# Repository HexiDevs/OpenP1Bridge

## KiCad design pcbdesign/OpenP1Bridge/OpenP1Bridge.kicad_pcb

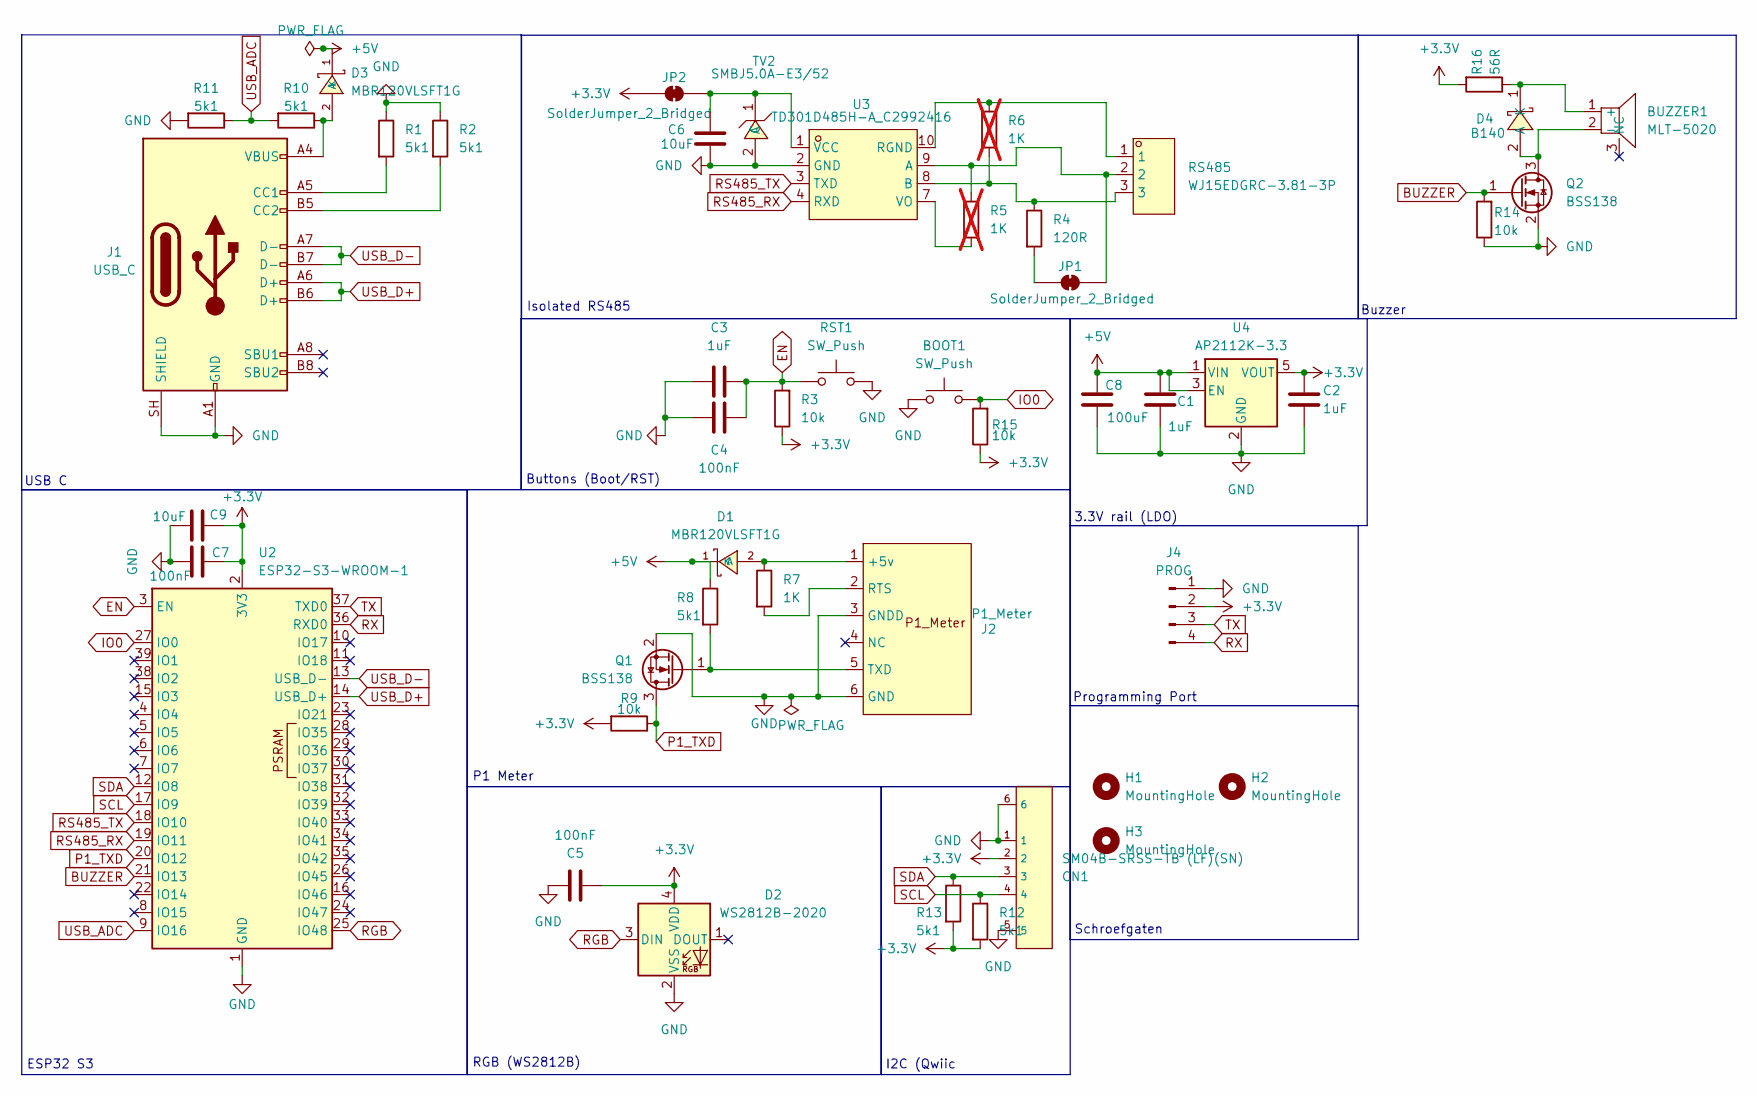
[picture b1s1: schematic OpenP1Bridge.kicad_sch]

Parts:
BOOT1: SW_Push; SW_SPST_B3U-1000P
BUZZER1: MLT-5020; BUZ-SMD_L5.0-W5.5-P4.60; MPN MLT-5020; LCSC Part C94598
C1, C2: 1uF; C_0805_2012Metric
C3: 1uF; C_0603_1608Metric
C4, C5, C7: 100nF; C_0603_1608Metric
C6, C9: 10uF; C_0805_2012Metric
C8: 100uF; C_1206_3216Metric
CN1: SM04B-SRSS-TB (LF)(SN); C160404_CONN-SMD_4P-P1_00_SM04B-SRSS-TB-LF-SN; LCSC C160404
D1, D3: MBR120VLSFT1G; C223608_SOD-123F_L2_8-W1_8-LS3_7-RD; LCSC C223608
D2: WS2812B-2020; LED_WS2812B-2020_PLCC4_2.0x2.0mm
D4: B140; SMA_L4.3-W2.6-LS5.1-RD; MPN B140; LCSC Part C42414246
H1, H2, H3: MountingHole; MountingHole_3.2mm_M3_DIN965_Pad
J1: USB_C; USB_C_Receptacle_GCT_USB4105-xx-A_16P_TopMnt_Horizontal
J2: P1_Meter; P1_SolderPads
J4: PROG; Prog_pad
JP1, JP2: SolderJumper_2_Bridged; SolderJumper-2_P1.3mm_Bridged_RoundedPad1.0x1.5mm
Q1, Q2: BSS138; SOT-23
R1, R2, R8, R10, R11, R12, R13: 5k1; R_0603_1608Metric
R3, R9, R14, R15: 10k; R_0603_1608Metric
R4: 120R; R_1206_3216Metric
R5, R6: 1K; R_0805_2012Metric; not fitted
R7: 1K; R_0805_2012Metric
R16: 56R; R_0603_1608Metric
RS485: WJ15EDGRC-3.81-3P; CONN-TH_3P-P3.81_WJ15EDGRC-3.81-3P; MPN WJ15EDGRC-3.81-03P-14-00A; LCSC Part C8406
RST1: SW_Push; SW_SPST_B3U-1000P
TV2: SMBJ5.0A-E3/52; SMB_L4.6-W3.6-LS5.3-RD; MPN SMBJ5.0A-E3/52; LCSC Part C61069
U2: ESP32-S3-WROOM-1
U3: TD301D485H-A_C2992416; COMM-TH_TD301D485H-A-2; MPN TD301D485H-A; LCSC Part C2992416
U4: AP2112K-3.3; SOT-23-5

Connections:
+3.3V: C2.1, C5.2, C7.2, C9.2, CN1.2, D2.4 (VDD), J4.2, JP2.2 (B), R3.1, R9.2, R12.2, R13.2, R15.1, R16.2, U2.2 (3V3), U4.5 (VOUT); also elsewhere on the board
+5V: C1.1, C8.1, D1.1 (K), D3.1 (K), R8.1, U4.1 (VIN), U4.3 (EN)
BUZZER: Q2.1 (G), R14.2, U2.21 (IO13)
EN: C3.2, C4.1, R3.2, RST1.1, U2.3 (EN)
GND: BOOT1.1, C1.2, C2.2, C3.1, C4.2, C5.1, C6.2, C7.1, C8.2, C9.1, CN1.1, CN1.5, CN1.6, D2.2 (VSS), J1.A1 (GND), J1.A12 (GND), J1.B1 (GND), J1.B12 (GND), J1.SH (SHIELD), J2.3 (GNDD), J2.6 (GND), J4.1, Q1.2 (S), Q2.2 (S), R1.1, R2.1, R11.2, R14.1, RST1.2, TV2.2 (A), U2.1 (GND), U2.40 (GND), U2.41 (GND), U3.2 (GND), U4.2 (GND); also elsewhere on the board
IO0: BOOT1.2, R15.2, U2.27 (IO0)
unnamed: BUZZER1.1 (+), D4.1 (K), R16.1
unnamed: BUZZER1.2 (-), D4.2 (A), Q2.3 (D)
unnamed: D1.2 (A), J2.1 (+5v), R7.1
unnamed: D3.2 (A), J1.A4 (VBUS), J1.A9 (VBUS), J1.B4 (VBUS), J1.B9 (VBUS), R10.1
unnamed: J1.A5 (CC1), R1.2
unnamed: J1.B5 (CC2), R2.2
unnamed: J2.2 (RTS), R7.2
unnamed: J2.5 (TXD), Q1.1 (G), R8.2
unnamed: JP1.1 (A), R5.1, RS485.2, U3.9 (A)
unnamed: JP1.2 (B), R4.2
unnamed: C6.1, JP2.1 (A), TV2.1 (C), U3.1 (VCC)
unnamed: R4.1, R6.2, RS485.3, U3.8 (B)
unnamed: R6.1, RS485.1, U3.10 (RGND)
unnamed: R5.2, U3.7 (VO)
P1_TXD: Q1.3 (D), R9.1, U2.20 (IO12)
RGB: D2.3 (DIN), U2.25 (IO48)
RS485_RX: U2.19 (IO11), U3.4 (RXD)
RS485_TX: U2.18 (IO10), U3.3 (TXD)
RX: J4.4, U2.36 (RXD0); also elsewhere on the board
SCL: CN1.4, R12.1, U2.17 (IO9)
SDA: CN1.3, R13.1, U2.12 (IO8)
TX: J4.3, U2.37 (TXD0); also elsewhere on the board
USB_ADC: R10.2, R11.1, U2.9 (IO16)
USB_D+: J1.A6 (D+), J1.B6 (D+), U2.14 (USB_D+)
USB_D-: J1.A7 (D-), J1.B7 (D-), U2.13 (USB_D-)

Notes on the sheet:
ESP32 S3
RGB (WS2812B)
I2C (Qwiic
Buzzer
Isolated RS485
P1 Meter
USB C
3.3V rail (LDO)
Buttons (Boot/RST)
Programming Port
Schroefgaten

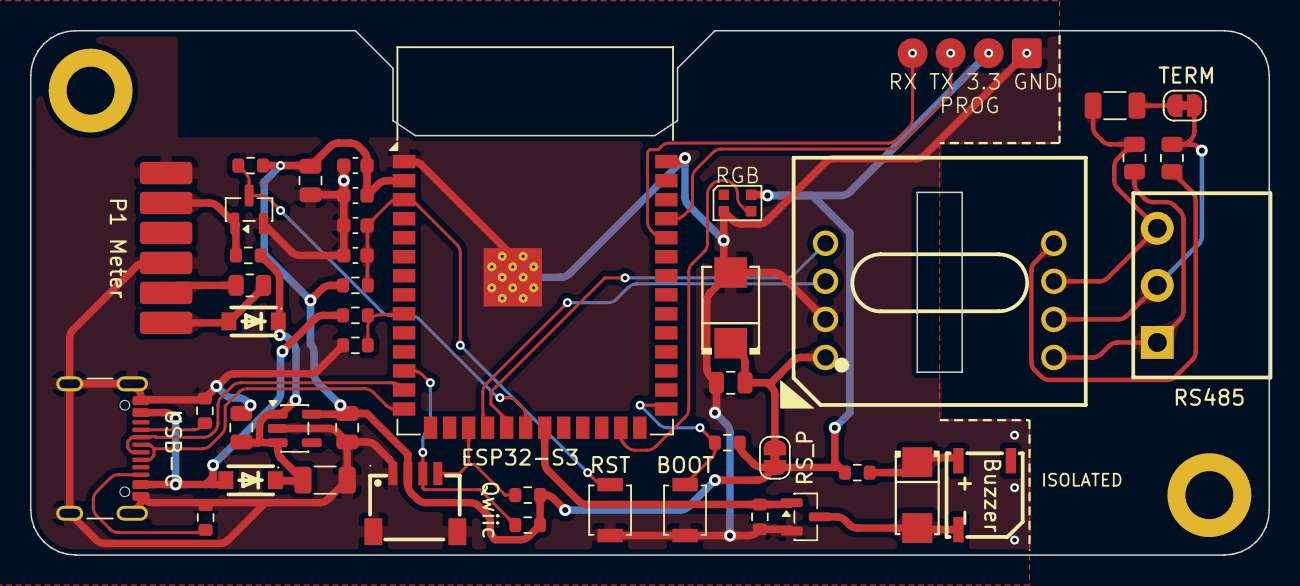
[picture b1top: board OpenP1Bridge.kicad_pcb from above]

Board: 2 copper layers, 82.7 x 35.0 mm, 47 parts (0 on the bottom side), 31 nets.

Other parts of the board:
PROG: PROG; Prog_pad

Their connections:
+3.3V: PROG.2; also elsewhere on the board
GND: PROG.1; also elsewhere on the board
RX: PROG.4; also elsewhere on the board
TX: PROG.3; also elsewhere on the board

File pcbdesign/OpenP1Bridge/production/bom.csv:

Designator,Footprint,Quantity,Value,LCSC Part #
"BOOT1, RST1",SW_SPST_B3U-1000P,2,SW_Push,
BUZZER1,BUZ-SMD_L5.0-W5.5-P4.60,1,MLT-5020,C94598
"C1, C2",0805,2,1uF,
C3,0603,1,1uF,
"C4, C5, C7",0603,3,100nF,
"C6, C9",0805,2,10uF,
C8,1206,1,100uF,
CN1,C160404_CONN-SMD_4P-P1_00_SM04B-SRSS-TB-LF-SN,1,SM04B-SRSS-TB (LF)(SN),C160404
"D1, D3",C223608_SOD-123F_L2_8-W1_8-LS3_7-RD,2,MBR120VLSFT1G,C223608
D2,LED_WS2812B-2020_PLCC4_2.0x2.0mm,1,WS2812B-2020,
D4,SMA_L4.3-W2.6-LS5.1-RD,1,B140,C42414246
J1,USB_C_Receptacle_GCT_USB4105-xx-A_16P_TopMnt_Horizontal,1,USB_C,
PROG,Prog_pad,1,PROG,
"Q1, Q2",SOT-23,2,BSS138,
"R1, R10, R11, R12, R13, R2, R8",0603,7,5k1,
"R14, R15, R3, R9",0603,4,10k,
R16,0603,1,56R,
R4,1206,1,120R,
R7,0805,1,1K,
RS485,CONN-TH_3P-P3.81_WJ15EDGRC-3.81-3P,1,WJ15EDGRC-3.81-3P,C8406
TV2,SMB_L4.6-W3.6-LS5.3-RD,1,SMBJ5.0A-E3/52,C61069
U2,ESP32-S3-WROOM-1,1,ESP32-S3-WROOM-1,
U3,COMM-TH_TD301D485H-A-2,1,TD301D485H-A_C2992416,C2992416
U4,SOT-23-5,1,AP2112K-3.3,
